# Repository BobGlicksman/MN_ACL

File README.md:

# MN_ACL
## RFID based access control and monitoring system for Maker Nexus.
This repository contains hardware, software and test information 
related to the development of an access control system for
Maker Nexus.

Each member is issued an RFID card that has been prepared to identify the member
and to ensure that cards can be revoked and/or replaced.  Membership information relevant
to card issuance and to member check-in and permission to access certain equipment
is supplied via real-time
query of the Maker Nexus CRM system which uses EZ Facility.  The code to access EZ Facility
via their REST API has been broken out into separate functions so that it can be replaced
by any suitable database.  Administrative utilities are also provided to facilitate recycling
membership RFID cards and identifying the owner of misplaced RFID cards.

A "Facility Database", separate from EZ Facility, is included in this project.  EZ Facility is the
authoritative source for all membership status, payment and training information needed for access
control decisions.  The Facility Database provides membership access records for both a real-time 
status display and for off-line reporting on facility and equipment utilization.

This project uses a Particle Argon; however, a Xenon should also work in a Particle Mesh configuration.  
The access control system is based upon Mifare Classic 1K RFID cards that are written to/read from
using a PN532-based MFC/RFID breakout board.  The Adafruit PN532 library is used to supply
the underlying communication support between the Particle device and the RFID card. Mifare Classic 1K 
cards have been chosen because they are inexpensive and widely available on the Internet.
These cards are older technology and not very secure.  However, we have deemed them to be secure 
enough for this application.  One sector of the card is chosen for this application and the sector encryption
keys and block access control bits are changed to make the card data secure from casual inspection and
from cloning.  The
remaining sectors of the card can be used for other applications, e.g. vending machine credits or special room
access.

A detailed technical overview of this project is provided in Documents/RFID_ACS_Overview_Document.pdf.  
We strongly encourage you to read through his document before deciding how this project might be
applied to your unique access control and monitoring situation.

## Files and Folders:
#### README.md:  
This document.
#### Repository_Overview.pdf:  
An overview of the structure and contents of this repository.
#### Terms_Of_Use_License_and_Disclaimer.pdf:  
You MUST READ this document and AGREE TO 
its terms and conditions before you are authorized to use the material in this repository. This
project is released under and open source, non-commercial license.
### Documents (folder):
Project documentation, including the RFID_ACS_Overview_Document and build, install and
usage documents.
### Hardware (folder): 
Design information (CAD files) and documentation for all of the hardware used
in this project, including electronic design, printed circuit board design, and
mechanical/packaging design and build information.
### Software (folder):
Design information, documentation, source and executable code for all of the software
in this project, including Particle (Argon) software, webhooks, PHP files, database
schema and stored procedures, Android app source and executable files, and web/html
files.
### Test and Development (folder):
Legacy test code and test results for integrating RFID cards and EZ Facility API calls with 
Particle devices.  The information in this folder is not necessary to build or install
this project.  However, it may be useful for developing extent ions to the RFID and/or EZ Facility
capabilities of this project.

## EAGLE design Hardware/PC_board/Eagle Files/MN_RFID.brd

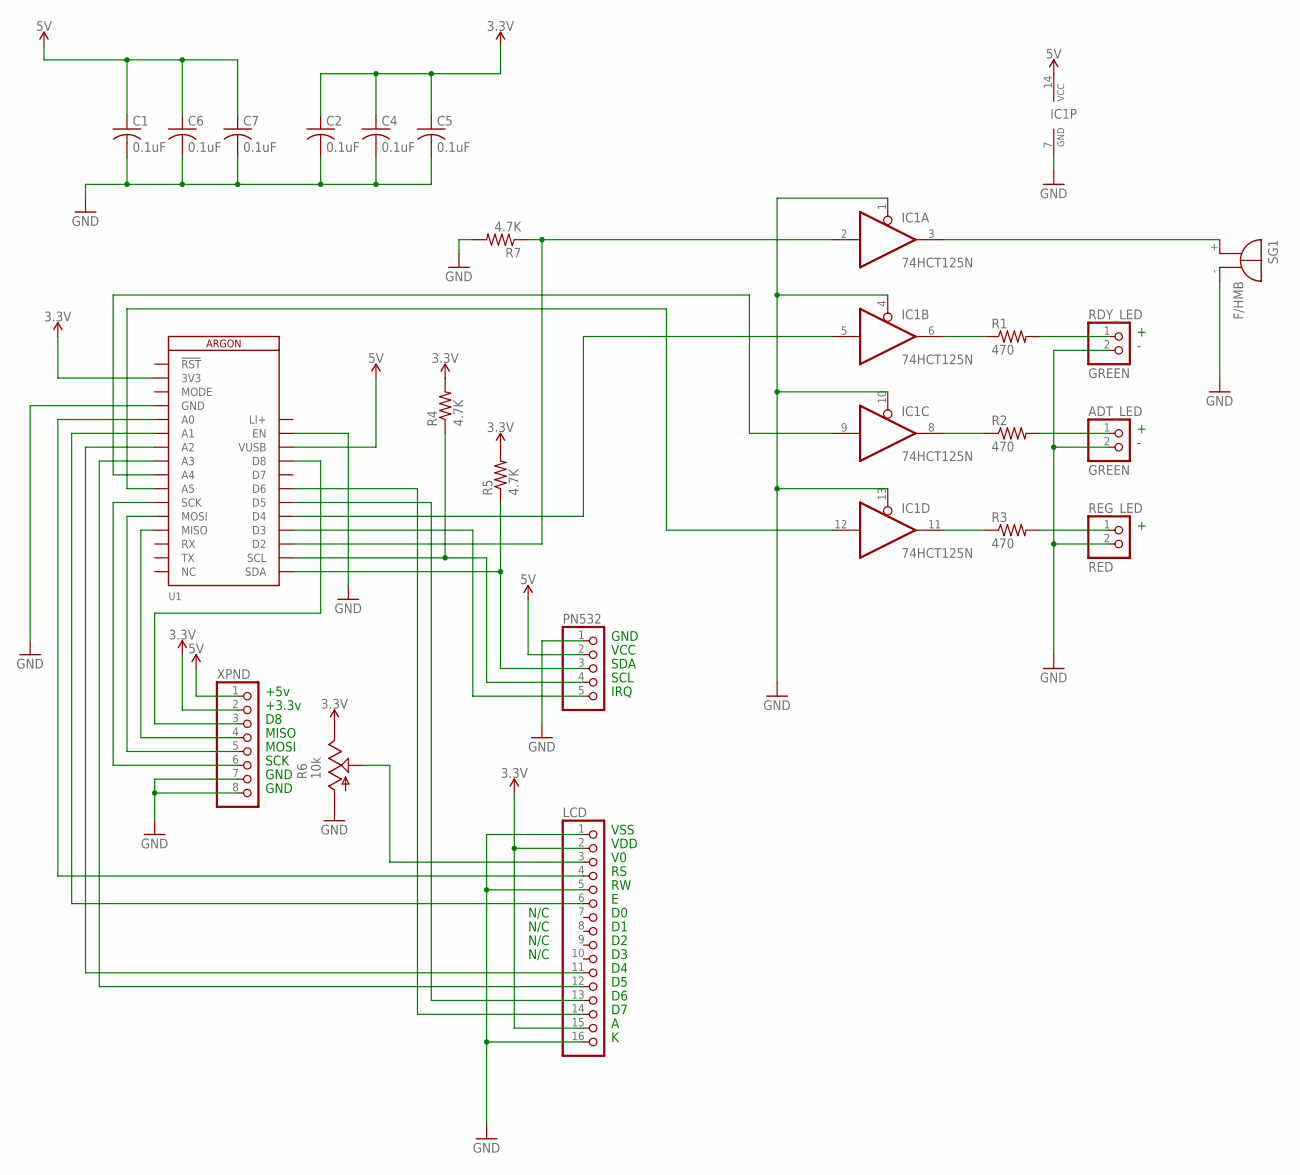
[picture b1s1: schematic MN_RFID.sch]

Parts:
ADT_LED: GREEN; 1X02
C1, C2, C4, C5, C6, C7: 0.1uF; C025-024X044
IC1: 74HCT125N; DIL14
LCD: PINHD-1X16; 1X16
PN532: PINHD-1X5; 1X05
R1, R2, R3: 470; 0204/7
R4, R5, R7: 4.7K; 0204/7
R6: 10k; CT6
RDY_LED: GREEN; 1X02
REG_LED: RED; 1X02
SG1: F/HMB
U1: ARGON
XPND: PINHD-1X8BIG; 1X08-BIG

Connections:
3.3V: C2.1, C4.1, C5.1, LCD.2, LCD.15, R4.2, R5.2, R6.E, U1.2 (3V3), XPND.2
5V: C1.1, C6.1, C7.1, IC1.14 (VCC), PN532.2, U1.26 (VUSB), XPND.1
GND: ADT_LED.2, C1.2, C2.2, C4.2, C5.2, C6.2, C7.2, IC1.1 (OE), IC1.4 (OE), IC1.7 (GND), IC1.10 (OE), IC1.13 (OE), LCD.1, LCD.5, LCD.16, PN532.1, R6.A, R7.2, RDY_LED.2, REG_LED.2, SG1.-, U1.4 (GND), U1.27 (EN), XPND.7, XPND.8
LI+: U1.28 (LI+)
unnamed: IC1.3 (O), SG1.+
unnamed: IC1.6 (O), R1.1
unnamed: IC1.8 (O), R2.1
unnamed: IC1.11 (O), R3.1
unnamed: R1.2, RDY_LED.1
unnamed: ADT_LED.1, R2.2
unnamed: R3.2, REG_LED.1
unnamed: LCD.4, U1.5 (A0)
unnamed: LCD.6, U1.6 (A1)
unnamed: LCD.11, U1.7 (A2)
unnamed: LCD.12, U1.8 (A3)
unnamed: LCD.13, U1.22 (D5)
unnamed: LCD.14, U1.23 (D6)
unnamed: PN532.4, R4.1, U1.18 (SCL)
unnamed: IC1.9 (I), U1.9 (A4)
unnamed: PN532.3, R5.1, U1.17 (SDA)
unnamed: LCD.3, R6.S
unnamed: PN532.5, U1.20 (D3)
unnamed: U1.25 (D8), XPND.3
unnamed: IC1.5 (I), U1.21 (D4)
unnamed: IC1.12 (I), U1.10 (A5)
unnamed: IC1.2 (I), R7.1, U1.19 (D2)
unnamed: U1.13 (MISO), XPND.4
unnamed: U1.12 (MOSI), XPND.5
unnamed: U1.11 (SCK), XPND.6

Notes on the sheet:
VSS
VDD
GND
VCC
SDA
SCL
IRQ
N/C
+5v
+3.3v
MISO
MOSI
SCK

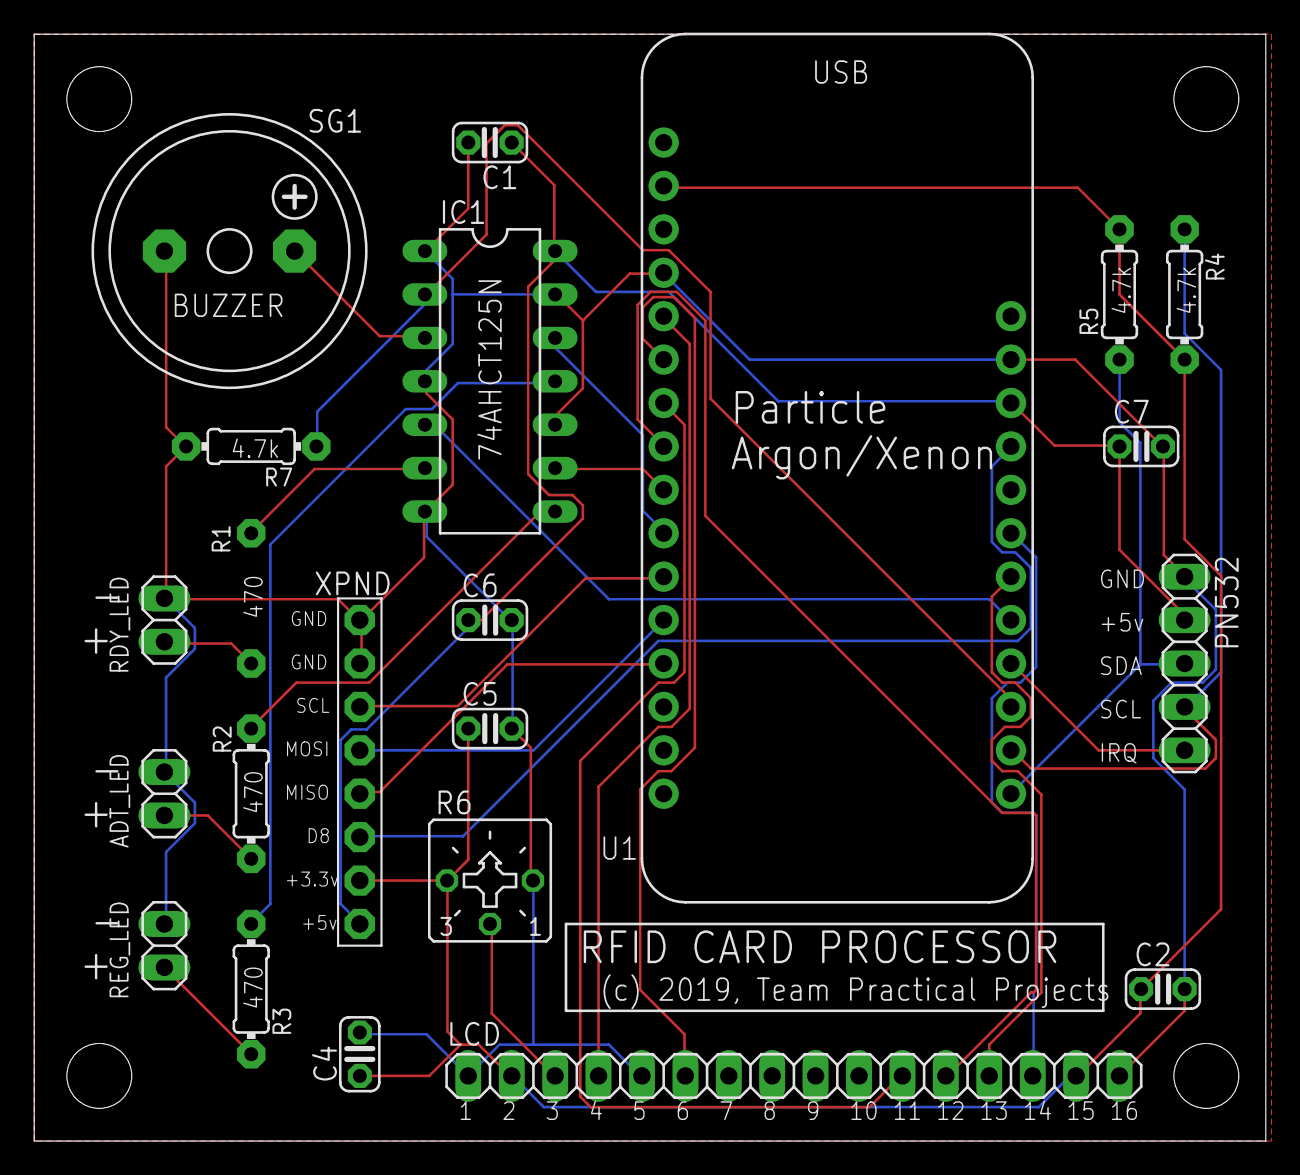
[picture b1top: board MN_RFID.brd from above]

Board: 2 copper layers, 72.1 x 64.8 mm, 22 parts (1 on the bottom side), 28 nets.

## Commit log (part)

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2019-06-19 Board config and initial test
    An Adafruit PN532 breakout board is connected to a Photon using I2C. The firmware runs a basic test that connects to the breakout board, reads out its firmware version and awaits for an RFID card to 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
2019-06-19 Initial Readme
2019-06-24 Create test-PN532-keyChange.ino
    This is a test for building the sector trailer with new keys and new access control bits. The sector trailer is not changed in this test -- the data is written to a data block and read back to make s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
2019-06-26 Update test-PN532-keyChange.ino
    Restructured code. This test version checks block authentication of relative blocks 0 and 1 using both default keys and the MN secret keys.
2019-06-27 Update test-PN532-keyChange.ino
    Fixed the testCard() function so that it resets after authentication failure and also only tries key A for authentication (so that it can be used in any app -- doesn't need to know secret key B - the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
2019-06-28 Update test-PN532-keyChange.ino
    Added test for writing using key B and then reading back using key A
2019-06-29 Finalized test-PN532-keyChange
    Finalized and tested the firmware. Posted a set of test results. NOTE: the test results are fine, but commenting out #define DEBUG does not eliminate all of the debug messages.
2019-06-29 test-PN532-keyChange.ino v2.1
    commenting out #define DEBUG in version 2.0 did not remove the test printout code. Changing DEBUG to TEST works fine. This is the only change from v2.0. I also included a printout of the results with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
2019-07-18 first check in of my working code.
2019-08-03 Preliminary Reader PCB Files
    Eagle files + PDF form of the schematic. The schemtic is complete and reading for testing on a breadboard. Board layout has not been started.
2019-08-06 first version with RFID and EZF code. Note #defines that enable RFID and LCD functionality
2019-08-07 first working version. will read card and checkin member. no uid test.
2019-08-08 Updated Schematic
    Updated schematic per testing breadboard at MN 8/07/19. Decided to power from Argon and remove external 5v USB connector, 3.3v power converter, and 100 uF cap. 5v supplied from Argon via VUSB pin. 3.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
2019-08-08 Update MN_RFID.brd
    Jiggled around the layout a little.
2019-08-08 Updated schematic
    Changed pull-up/down resistors from 5.6K to 4.7K -- more common value.
2019-08-10 Cleaned up initial readCard implementation. Added test for bad read and buzz. LCD messages changed. No longer blocks waiting for card.
2019-08-10 1.02 Rewrote to put all of state machine in main loop. Soooo much cleaner now.
2019-08-12 Update MN_RFID.brd
    Added some addtional text to top silkscreen layer.
2019-08-12 updated header comments. version now 1.03
2019-08-12 Create Reader PCB Parts List.xlsx
    Preliminary parts list in Excel format - currently incomplete
2019-08-25 moved all LCD writes to a common routine
2019-08-25 added firmware update event
2019-08-25 added member name to the clientInfo structure and display it after good checkin
2019-08-25 LED handled correctly, more errors displayed, buzzer in places, welcome with client name
2019-08-28 Added parameters to particle calls to remove warnings. Now compiles without warnings.
2019-08-29 Updated Parts List
    renamed and updated the Excel parts list. Added in Jim's parts from EBay.
2019-08-31 get keys from cloud is implemented, but particle cloud does not respond. why?
2019-08-31 Cloud function to configure device type
2019-09-01 Added folder for Admin GUI App
    The folder contains Particle test code to test out the app. The GUI is an .aia file that is currently in design and development.
2019-09-02 Reordered setup() into sections. No significant changes to functionality.
2019-09-03 Admin query member and burn card work!
2019-09-04 Update CardWriterGUITester.ino
    Fixed up strings to make proper JSON format.
2019-09-05 Update MN_Card_Administration.aia
    Have the get member information part mostly working. The code works but I need to parse the JSON response and load the clientID into the appropraite field writing a card.
2019-09-07 Completed Admin GUI App
    .apk and .aia files are in the AdminGUI folder. An updated .ino test program source file is also enclosed.
2019-09-19 1.07 oAuth token request in setup(). Version string. Card identification working.
2019-09-20 1.071 bug fix to the timeout code after displaying a query name
2019-09-21 1.074 fix to burnUID. Checkin test now validates UID, contract status, amount due.
2019-09-21 1.074 JSON returned to Admin on "card info" now includes "Checkin" which tells what would happen if the card was used at a checkin terminal
2019-09-24 1.081 removed amount due from JSON, added softer message. Firstname added to logdb.
2019-09-29 fixed bug in cloudIdentifyCard
2019-09-29 added some dblog and custom LCD msg in readCard
2019-10-02 updates to the reporting website :
2019-10-03 Update RFID_R1.brd
    Slight adjustments and additions to top silkscreen to make the board look good as rendered by OSHPark.
2019-10-04 moved rfid keys to an include file
2019-10-04 refactoring web site
2019-10-04 Update MN_Card_Administration.aia
    Uodated to version 1.1 of the API document. Still need to implement timeout (max tries) on queryMember() and identifyCard()
2019-10-04 Update MN_Card_Administration.apk
    Updated to API spec version 1.1. Still need to implement max # tries for queryMember() and identifyCard()
2019-10-05 Update CardWriterGUITester.ino
    Updated to latest API spec v1.2 10/5/19
2019-10-06 1.084 resetCard works. "ing" denial bug fixed.
2019-10-07 JSON to app bug fixed
2019-10-07 Bug Fix - v 1.2
    Changed tag name from Client ID to Member Number in cardInfo where it is the membership number that is returned.
2019-10-14 Limit LCD lines to 16 chars
2019-10-14 added comments
2019-10-18 1.09 split into include files
2019-10-20 website added checkin/checkout logging
2019-10-20 changed logging webhook to new target
2019-10-22 1.1 moved webhook callbacks to one function
2019-10-22 website manual checkout php
2019-10-23 Was checking in reboot events. Fixed strpos dumb
2019-10-23 on checkout store minutes active in db
2019-10-23 Uses new checkin/out events
2019-10-23 1.10 checkin/out shown on LCD now
2019-11-07 1.2 adds devtype 4 woodshop door
2019-11-11 updates to use the sandbox accounts
2019-11-11 corrected ezf login
2019-11-11 Test OK with keys
2019-11-13 Issue #15 fixed
2019-11-14 just changes to comments
2019-11-15 Hardware/Enclosure Files
    Reorganized the Hardware folder with subfolders for PCB and Enclosure. Added enclosure CAD files. photos, and notes for later document development. Renamed the Parts List spreadsheet to reflect that 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
2019-11-15 Update RFID_Station_Parts_List.xlsx
    Not complete but added Jim's parts and links
2019-11-17 turn on all LEDs when device type undefined
2019-11-19 New daily/weekly checkin reports
2019-11-21 Added preliminary and incomplete docs as placeholders
    Posted an incomplete and unreviewed version of an Overview doc. Also posted an old TOU doc. Both of these docs needs work before publication of this project!
2019-11-27 1.3 readTheCard enhancements
2019-11-27 issue #20. LCD now clears before update
2019-11-28 Reboots every day after 1:05 AM
2019-11-29 Gets token every hour between 8 and midnight
2019-12-01 1.41 added ShopBot to allowed-in wood packages
2019-12-06 relies on mustache template in webhook
2019-12-07 Updated app to make reset card work
    The cloud function name had changed. The app now calls to new resetCard() function.
2019-12-22 checkin report shows woodshop
2019-12-26 Update RFID_ACS_Overview_Document.docx
    First draft complete and ready for review.
2019-12-29 GetDeviceConfig.php
2019-12-29 renamed to GetStationConfig.php
2019-12-29 Webhook renamed GetStationConfig
2019-12-29 renamed API to have fdb prefix
2020-01-02 added lasers as device 105
2020-01-04 laser case file updated
2020-01-05 Released version of Overview document
    Deleted the in-review Word version and replaced with the reviewed and released document in PDF format.
2020-01-07 fdbGetStationConfig bug fixed
2020-01-07 devtypetostring handles all dev types now
2020-01-08 correct dev keys
2020-01-09 1.52 parses ok keywords
2020-01-11 updated rfid web config to remove usernames
2020-01-11 current checkin webpage - needs db stored proc
2020-01-11 small bug fix
2020-01-11 SetDeviceType now delays reboot to return a value.
2020-01-12 adds new report to home page
2020-01-13 Version 2 of Station Config App
    This version of the app does not hardcode the fdb URL. Rather, the URL is entered in a textbox on the Setup screen and then is saved in the tinyDB. When the app is opened, or Setup is exited, the URL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
2020-01-15 Update RFID_ACS_Overview_Document.pdf
    Added info about station security and staton config in the facility DB
2020-01-16 Update RFID_ACS_Overview_Document.pdf
    Incorporated Jim's comments
2020-01-17 doing the deletes
2020-01-19 Delete argon_firmware_1579475600036.bin
    deleted old test local compile files
2020-01-20 Document placeholders
    Updated README.m and added placeholders for documentation.
2020-01-22 deleted. old per bob g
2020-01-22 FDB documentation
2020-01-30 added unique members last 90 days
2020-02-06 Phoptos ready for documents
2020-02-11 1.6 added last name to fdb logging
2020-02-11 moved fdb schema files
2020-02-14 deleted development test files
2020-02-14 new manual
2020-02-15 added 60 day unique user count
2020-02-15 added get display classes from clientID
2020-02-15 Update sp_insert_update_clientInfo.sql
    added BEGIN so the procedure is not dropped if the stored proc does not compile
2020-02-15 added database reference
2020-02-21 report now excludes staff members
2020-02-26 adds last name to fdb and maintains clientInfo tbl
2020-02-27 setDevType now works for type 0
2020-02-29 Updated docs for release
    Reviewed a number of documents. Updated the TOU document; the others are OK as is.
2020-06-04 1.7 add checkin event for lockbox
2020-06-13 Synched with Jim (latest version)
2020-06-19 Updated Station Config App to v2.1
    Disabled the station code text box so that device/listen codes can only be selected from the list obtained from the fdb. This resolves the bug that crashes the app if someone types in an unassigned t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
2020-06-19 V2.2 of Station Config App
    I noticed a cosmetic probem with the app and I cleaned it up. Previously, there was a label for the new station type and another for the new listen type. With the current GUI having one new type code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
2020-06-21 Removed blank graphs.
2020-06-25 Update RFID_Administrator_User_Manual.pdf
    Revised to include instructions for RFID Lock devices
2020-07-01 Update RFID_ACS_Overview_Document.pdf
    Incorporated Jim's suggested edit
2020-08-20 v1.73 event secret; new production define
2020-08-20 clean up of files not needed in git
2020-08-20 added gitignore
2020-12-17 1.8 bug in client info receive
2021-02-14 fix: duplicate person on checkin screen w no name
2021-02-14 removed extra DELIMITER command
2021-04-22 1.9 debugX events disabled
2021-07-01 added a report on one clientID
2021-08-10 2.0 attempted fix for github #79
2021-09-12 Fixed MD Formatting errors
2021-09-12 Update EZFLocalMemberCache_Proposal.md
    comments at the end of the file by me.
2021-09-14 2.1 update ArduinoJSON
2021-09-14 turning back off Production Compile flag
2021-09-30 ezfClientByClientID to use mustache code
2021-10-08 v2.2 compiles
2021-10-10 v2.3 on token error, wait for RFID card tap
2021-10-10 webhook update
2021-10-26 settings.json
2021-11-08 correct photo size now
2021-11-08 removed a settings.json that should not be in repo

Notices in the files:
Hardware/PC_board/Eagle Files/MN_RFID.brd:
(c) 2019, Team Practical Projects
parts and their libraries:
Particle-Devices: Licensing: Designed by Particle.
SparkFun-PowerSymbols: Licensing: Creative Commons ShareAlike 4.0 International - https://creativecommons.org/licenses/by-sa/4.0
